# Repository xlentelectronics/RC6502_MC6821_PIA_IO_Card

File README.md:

# RC6502 MC6821 PIA IO Card

To provide I/O capabilities with the RC6502, an I/O card with the MC6821 PIA has been developed. To connect the card to the RC6502, simply insert it into the backplane. You can place the card in the desired address range using jumper J4. The included software samples use the base address $C000. The hardware and software have been developed under an open license.

# Software Examples
In the Software Example folder are some examples how to use the MC6821 PIA IO Card. The examples are created for Krusader v1.3 and for MBASIC.

## Krusader assembler Example
In the Krusader Assembler folder the example MC6821_PingPong_Light_Speedmeter_Color.asm can be found.  This is a fully compatible Krusader v1.3 program. The program lets 8 LEDS running in a pingpong way. The speed can be controlled via the + and - of the numeric keypad of the keyboard.

The following hardware connection must be made to PORTA and PORTB. PORTA is connected to 8 LEDs. The anode of the LEDs is connected with a 1 kΩ resistor between Vcc and the corresponding pins PA0 through PA7. The .asm file can be loaded directly into Krusader v1.3. Make sure you have opened Krusader in edit mode (000) before loading the .asm file. If you use TeraTerm, you load the .asm via _Send file ..._ After successful load, assembler the file and run it via R $0300 (I assume you know how Krusader v1.3 works)

There is also as example the MC6821_PingPong_Light_Speedmeter_Color.woz. This file is the WoZ monitor compatible file. You can load the .woz file from the Woz Monitor in the same way by using _Send file ..._  

## MBASIC Examples
In the MBASIC folder there are 2 MBASIC examples, MBasic_MC6821_PIA_IO_RunningLight_PortA.bas and MBasic_MC6821_PIA_IO_RunningLight_Speed.bas.

Both MBASIC examples uses the same LED hardware connections as mentioned for the PINGPONG Running Light. An additional piece of hardware is required for the MBasic_MC6821_PIA_IO_RunningLight_Speed.bas.
Connect a push button via 10K resistor to Vcc and the other lead of the push button to GND. Connect PORTB PB7 to the 10K resistor. When you push the button, PB7 will go low.

Start MBASIC and load the .bas file via _Send file ..._ and type RUN to execute the program.

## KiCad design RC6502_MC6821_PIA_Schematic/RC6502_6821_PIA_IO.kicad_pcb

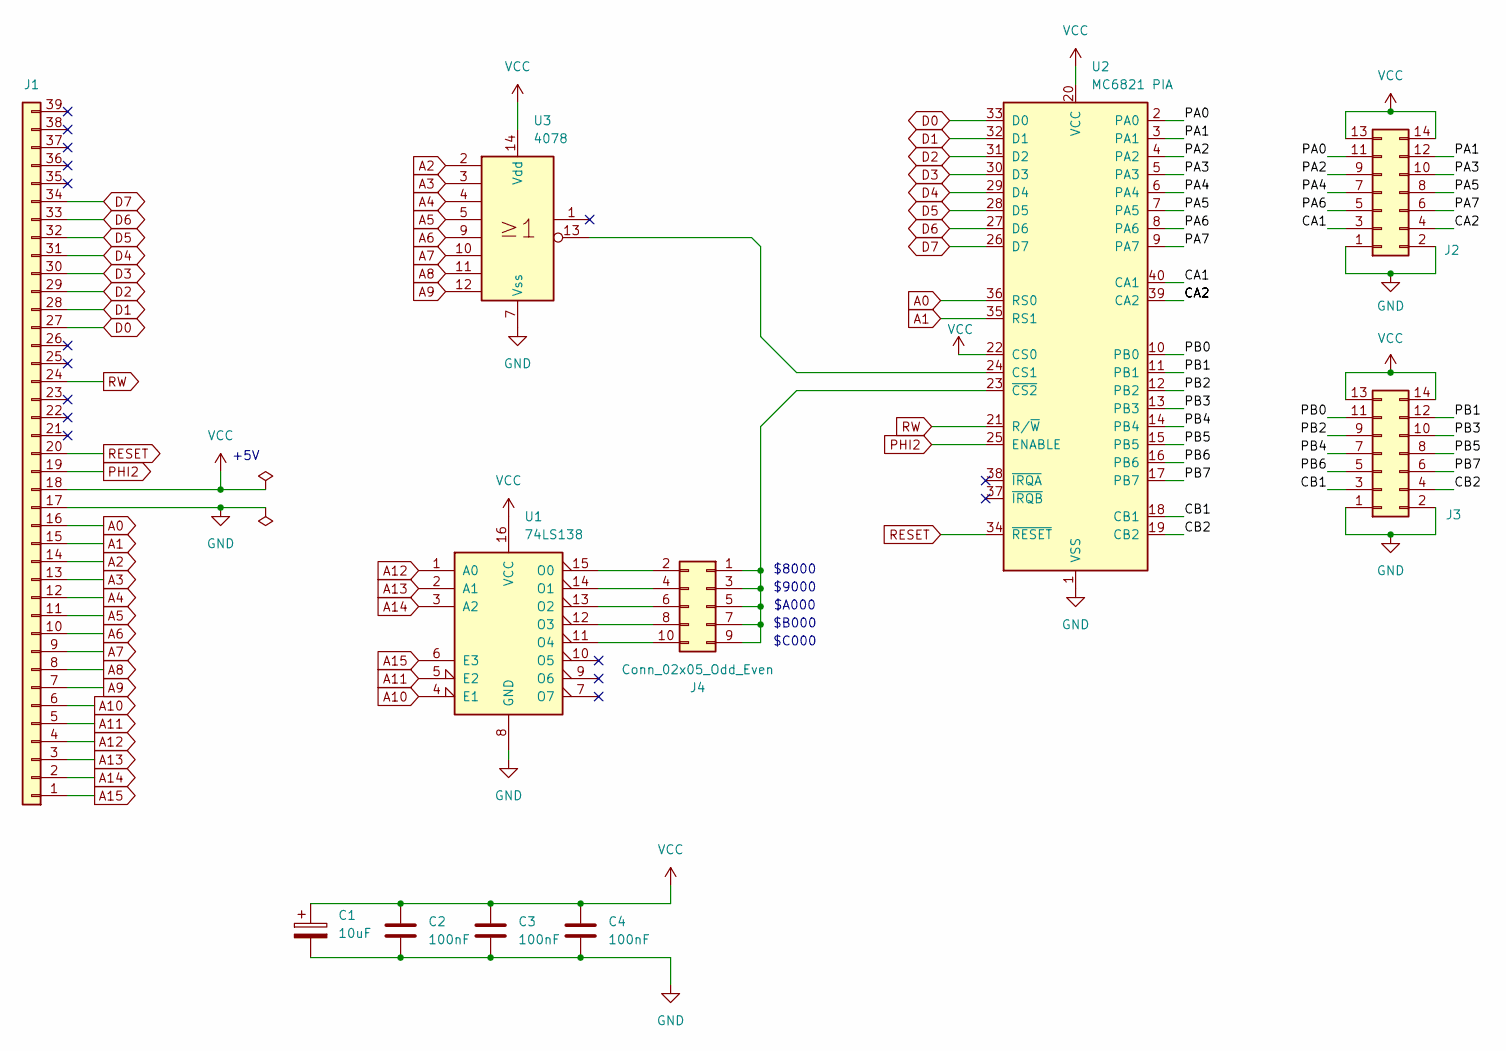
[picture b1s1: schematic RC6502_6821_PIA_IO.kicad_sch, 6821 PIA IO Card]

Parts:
C1: 10uF; CP_Radial_D6.3mm_P2.50mm
C2: 100nF; C_Disc_D3.0mm_W1.6mm_P2.50mm
C3, C4: 100nF; C_Disc_D4.3mm_W1.9mm_P5.00mm
J1: Conn_01x39; PinHeader_1x39_P2.54mm_Horizontal
J2, J3: Conn_02x07_Odd_Even; PinHeader_2x07_P2.54mm_Vertical
J4: Conn_02x05_Odd_Even; PinHeader_2x05_P2.54mm_Vertical
U1: 74LS138; DIP-16_W7.62mm
U2: MC6821 PIA; DIP-40_W15.24mm
U3: 4078; DIP-14_W7.62mm

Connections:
/CA1: J2.3, U2.40 (CA1)
/CA2: J2.4, U2.39 (CA2)
/CB1: J3.3, U2.18 (CB1)
/CB2: J3.4, U2.19 (CB2)
/PA0: J2.11, U2.2 (PA0)
/PA1: J2.12, U2.3 (PA1)
/PA2: J2.9, U2.4 (PA2)
/PA3: J2.10, U2.5 (PA3)
/PA4: J2.7, U2.6 (PA4)
/PA5: J2.8, U2.7 (PA5)
/PA6: J2.5, U2.8 (PA6)
/PA7: J2.6, U2.9 (PA7)
/PB0: J3.11, U2.10 (PB0)
/PB1: J3.12, U2.11 (PB1)
/PB2: J3.9, U2.12 (PB2)
/PB3: J3.10, U2.13 (PB3)
/PB4: J3.7, U2.14 (PB4)
/PB5: J3.8, U2.15 (PB5)
/PB6: J3.5, U2.16 (PB6)
/PB7: J3.6, U2.17 (PB7)
A0: J1.16, U2.36 (RS0)
A1: J1.15, U2.35 (RS1)
A2: J1.14, U3.2
A3: J1.13, U3.3
A4: J1.12, U3.4
A5: J1.11, U3.5
A6: J1.10, U3.9
A7: J1.9, U3.10
A8: J1.8, U3.11
A9: J1.7, U3.12
A10: J1.6, U1.4 (E1)
A11: J1.5, U1.5 (E2)
A12: J1.4, U1.1 (A0)
A13: J1.3, U1.2 (A1)
A14: J1.2, U1.3 (A2)
A15: J1.1, U1.6 (E3)
D0: J1.27, U2.33 (D0)
D1: J1.28, U2.32 (D1)
D2: J1.29, U2.31 (D2)
D3: J1.30, U2.30 (D3)
D4: J1.31, U2.29 (D4)
D5: J1.32, U2.28 (D5)
D6: J1.33, U2.27 (D6)
D7: J1.34, U2.26 (D7)
GND: C1.2, C2.2, C3.2, C4.2, J1.17, J2.1, J2.2, J3.1, J3.2, U1.8 (GND), U2.1 (VSS), U3.7 (Vss)
unnamed: J4.1, J4.3, J4.5, J4.7, J4.9, U2.23 (~CS2)
unnamed: J4.2, U1.15 (O0)
unnamed: J4.4, U1.14 (O1)
unnamed: J4.6, U1.13 (O2)
unnamed: J4.8, U1.12 (O3)
unnamed: J4.10, U1.11 (O4)
unnamed: U2.24 (CS1), U3.13
PHI2: J1.19, U2.25 (ENABLE)
RESET: J1.20, U2.34 (~RESET)
RW: J1.24, U2.21 (R/~W)
VCC: C1.1, C2.1, C3.1, C4.1, J1.18, J2.13, J2.14, J3.13, J3.14, U1.16 (VCC), U2.20 (VCC), U2.22 (CS0), U3.14 (Vdd)

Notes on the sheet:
$9000
$B000
$C000
$8000
$A000
+5V

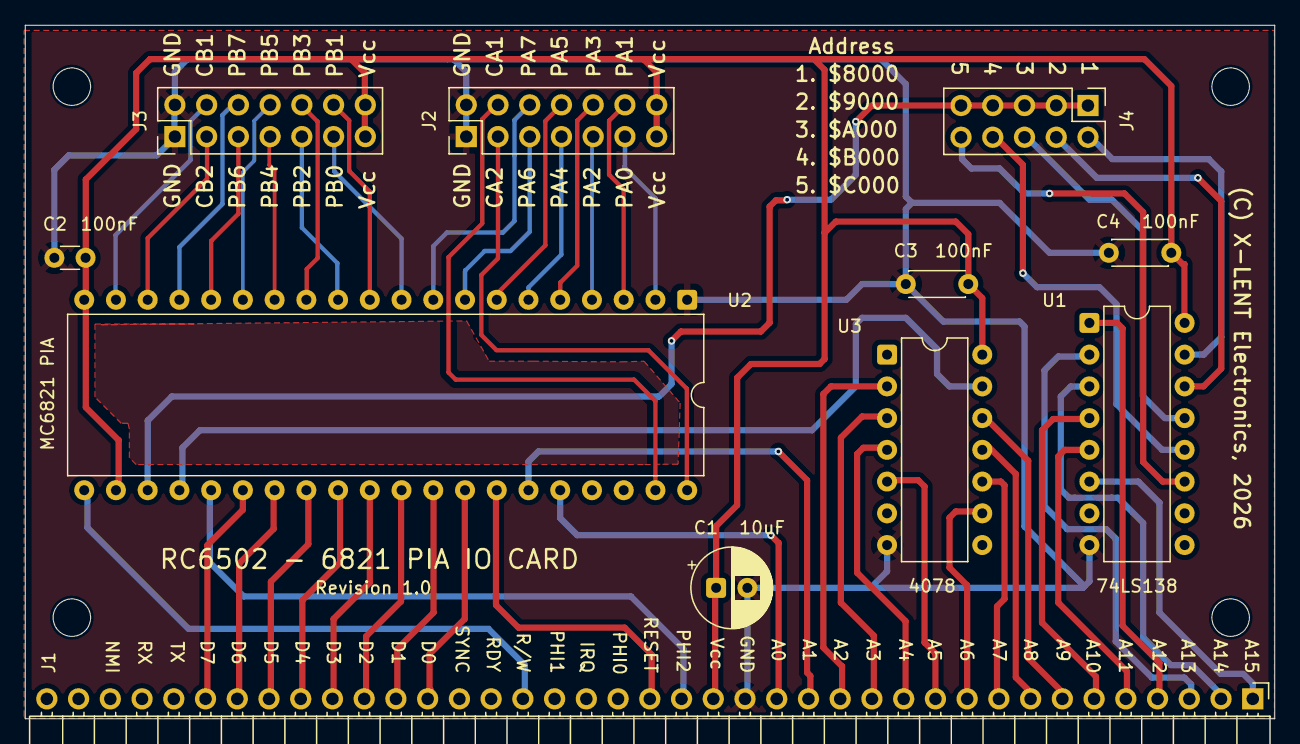
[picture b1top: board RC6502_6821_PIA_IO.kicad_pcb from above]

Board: 2 copper layers, 100.0 x 55.5 mm, 11 parts (0 on the bottom side), 56 nets.

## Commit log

2026-03-29 First upload
    Uploading project to GitHub
2026-03-29 Upload
2026-03-29 Update README.md
    Textual correction
2026-04-18 Update
    Added to enter Base Address
